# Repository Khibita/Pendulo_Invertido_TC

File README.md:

# 🧩 Proyecto: Péndulo Invertido

## 📋 Introducción
Este proyecto se centra en diseñar, construir y poner en marcha un péndulo invertido. Este es un sistema muy conocido en ingeniería de control porque es un ejemplo clásico de un sistema que no es lineal, es inestable y además tiene doble integración. 

El péndulo invertido presenta un desafío interesante, ya que hay que crear un sistema de control capaz de mantenerlo en equilibrio vertical desde cualquier posición inicial y frente a perturbaciones externas. Para lograrlo, se ha implementado un controlador PID usando un microcontrolador ESP32, apoyado por sensores de orientación como acelerómetro y giroscopio, y un sistema de actuadores con motores DC. 

Durante el desarrollo del proyecto, se han trabajado distintas áreas como:
- [ ] el diseño y fabricación del sistema mecánico con impresión 3D.
- [ ] la selección e integración de componentes electrónicos.
- [ ] la programación del controlador en el entorno Arduino y la sintonización del PID para validar el comportamiento del sistema.

Al final, se ha logrado crear un robot que puede mantenerse en posición vertical, resistir pequeñas perturbaciones y desplazarse controladamente. Todo el proceso está bien documentado y puedes consultarlo y reutilizarlo en este repositorio.

---

## 🎯 Objetivos
- [ ] Estabilidad en posición vertical (±5°)
- [ ] Compensación de empujones
- [ ] Arranque desde cualquier posición
- [ ] Implementación en ESP32
- [ ] Sintonización del PID

---

## 🛠️ Hardware
**Componentes usados:**
- [ ] ESP32: [WROOM 32D], elegimos está por su bajo costé, conexiones inalambricas y poder ejecutar codigo c.
- [ ] Sensor: [MPU9250], elegimos está por su bajo costé, y devolver aceleración en 9 ejes.
- [ ] Driver de motor: [TB6612FNG] se ajustaba a las caracteristicas necesarias
- [ ] Motores: [fz3176] Motor de corriente continua que se ajustaba al precio y potencia de consumo
- [ ] Batería: [ MN1604] Coloquialemente conocida de "petaca", produce 9V de alimentación, El sistema necesita más , conexión por cable, para siguie
- [ ] Regulador de Tensión: [LM7805]
- [ ] Condensador: [0.1uF y 0.2uf]
- [ ] Conectores entrada y salida :  3 de 2 pines.

-Recordar que tanto la conexión electrica , como la pcb se adjunta en este mismo repositorio.

---

## 🧱 Diseño mecánico
**Software de diseño usado:**  
- [ ] Para está pieza de geometría simple, pero que contaba con multiples caras, elegí freecad, debido que es con el estoy familiarizado por otras asignaturas y por tener entornos bien organizados y una comunidad activa. Aunque si es tu primera vez realizando este tipo de objetos con varias caras, te recomiendo aplicaciones con interfaces más modernas.

**Método de fabricación:**  
- [ ] Impresora 3D, en concreto la Anet A8. La impresión tardará bastante por culpa de los soportes, para reducir el tiempo, se podría probar o a inclinar la figura o rotar la figura para que el eje y quede como el eje x, precauición  son sujerencias no validadas. 

**Versiones del chasis y decisiones de diseño:**  
- [ ] Solo hay una versión, la publicada, en la cual prioricé que el centro de masas fuera lo más bajo posible y que estuviera centrado, apare de que no fuera necesario, tornillos más que para la placa base, aunque por como está  encastrada, no sería necesaría pasa su funcionamiento, recomiendo encarecidamente pornerlos.Para buscar un balance entre centro de masas bajo y porcentaje de ángulo de giro libre de las ruedas , sin que el chasis toque suelo, hice una incisio (diminuir el espesor a 1) en la parte baja del chasis un rectangulo para colocar la bateria , en caso de usar un portapilas más grande o una batería que superé las dimensiones de la usada habría que modificar el chasis.

---

## 🔌 Montaje
El montaje se divide en 2 partes:
- [ ] Soldar: soldar todos los componentes a la placa, en caso de querer reutilizar los componentes, recomiendo soldar conectores macho hembra a la placa en vez de los propios componentes. IMPORTANTE SEGUIR LAS DIRECCIONES DE LA PCB .
- [ ] Colocar las piezas: recomiendo empezar por la pcb una vez atornillada, seguir con los motores y por último pegar la batería con silicona al hueco posterior a la placa. 
---

## 📈 Control y software
**Controlador:** PID

**Implementación:**  
El lenguaje es .ino, compatible con  Esp32, pero las libreria en las que se basa, los pids a utilizar, está escrita en c++.

**Valores de cte del PID (Op 1 - reajustes pequeños en valores cercanos al (0,0), pero resistente a golpes fuertes):**  
- [ ] Kp = 50.0
- [ ] Ki = 1.0
- [ ] Kd = 20.0

**Valores de cte del PID (Op 1 - se mantiene quieto totalmente, pero sensible a golpes fuertes):**  
- [ ] Kp = 50.0
- [ ] Ki = 2.0
- [ ] Kd = 20.0

**PID Seleccionado**
- [ ] PID Filtrado, opción 3.

De forma resumida el codigo  compara el setpoint (posición destino) y la actual, a través del pid seleccionado, devuelve valores para los motores, que luego de ser normalizador , para enviar a los motores.

---

🎮 Control Inalambrico:

implementé la conexión por Bluetooth para que el sistema pudiera recibir órdenes en tiempo real desde un celular o una app, en mi caso serial terminal bluetooth, como si fuera un control remoto. Lo que hago es leer dos valores que llegan separados por una coma: uno controla el movimiento hacia adelante o atrás, y el otro el giro. Con esos datos, ajusto el setpoint del controlador PID para que el sistema se mueva según lo que el usuario indique, y también modifico la señal de los motores para que pueda girar fácilmente. Además, hice que el sistema mande de vuelta los valores recibidos por Bluetooth, así se puede ver desde el celular que la señal llegó bien y todo está funcionando como se espera.

---

## Resultados
**Hay que distingir dos casos según los valores de Kp, Ki, Kd elegidos:**
- [ ] Op 1:  El sistema llega conseguir estabilizarse en la mayoría de casos a golpes que incluso hagan tocar el suelo con el chasis. Una vez estabilizado empieza a tener pequeños sobre ajustes que hace que oscile un poco.
- [ ] Op 2:  El sistema consigue estabilizarse con golpes pequeños, pero en el caso de que el chasis toque suelo, no será capaz de conseguir levantarse de nuevo hasta chocar con algún objeto. Una vez estabilizado se mantiene estatico.

En resumen dependiendo de la respuestá deseada se puede elegir una u otra e incluso otras convinaciones de Kp, Ki y Kd. 

**Problemas con la Potencia**
- [ ] la conexión bluetooth hace que pierde algo de potencia los motores, por lo que es más sensible a perturbaciones, esto es debido a que el sistema no está pensado para una batería tan sencilla.
- [ ] Problemas de potencia, al romperseme los dos portapilas con que contaba tuve que hacer un arreglo con una batería de 9v auxiliar, por lo que se necesita conectar el robot a una fuente de energía. 

---

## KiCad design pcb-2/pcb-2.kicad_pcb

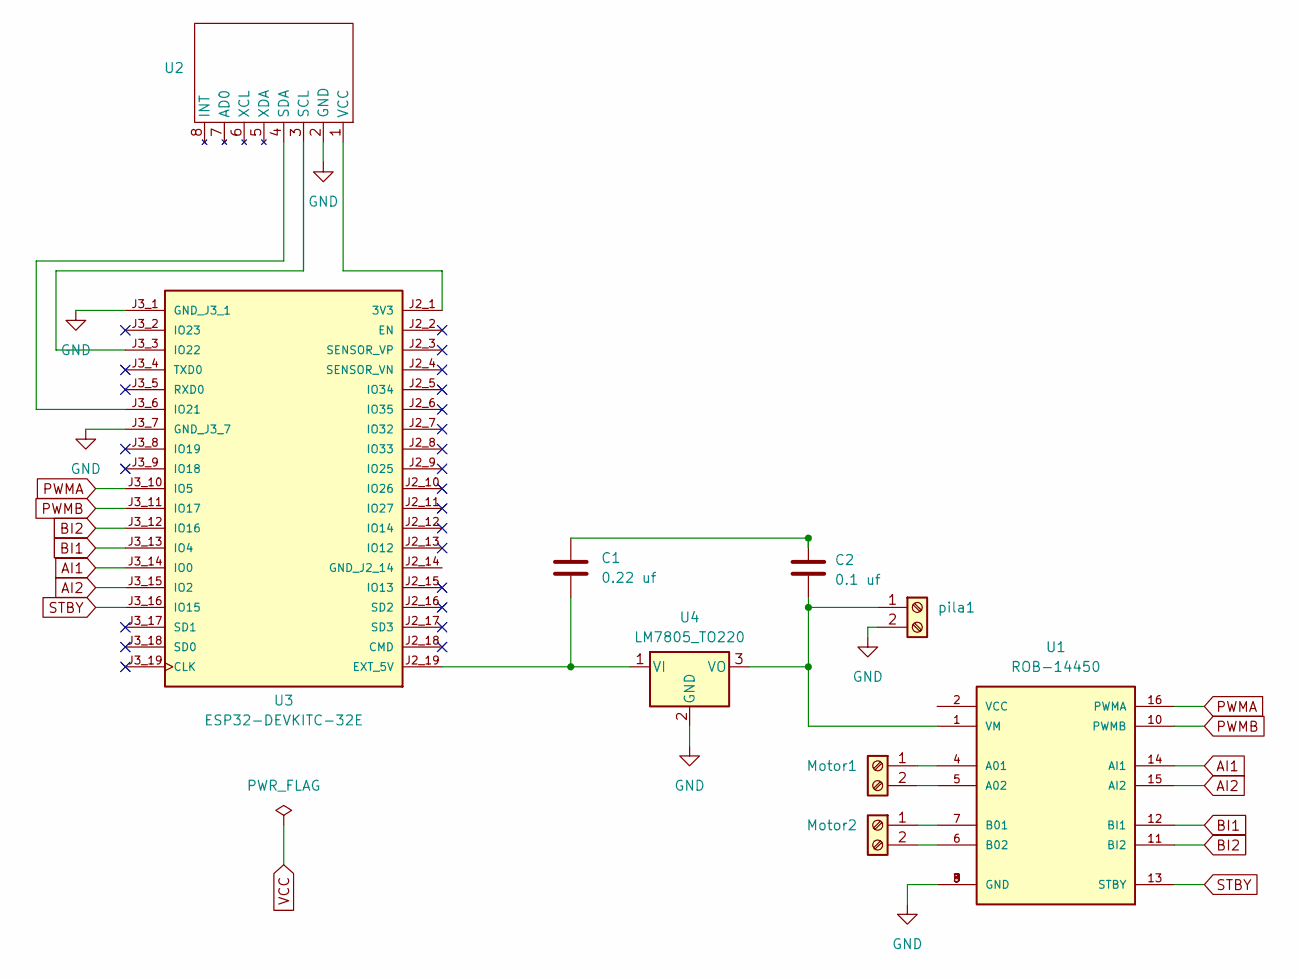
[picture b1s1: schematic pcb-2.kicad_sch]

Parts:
C1: 0.22 uf; CP_Radial_D5.0mm_P2.00mm
C2: 0.1 uf; CP_Radial_D5.0mm_P2.00mm
Motor1, Motor2: TerminalBlock_Phoenix_MKDS-1,5-2-5.08_1x02_P5.08mm_Horizont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
U1: ROB-14450; MODULE_ROB-14450; PARTREV 11-13-17
U2: MPU-6050
U3: ESP32-DEVKITC-32E; MODULE_ESP32-DEVKITC-32E; PARTREV 1.4
U4: LM7805_TO220; TO-220-3_Vertical
pila1: TerminalBlock_Phoenix_MKDS-1,5-2-5.08_1x02_P5.08mm_Horizont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

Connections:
AI1: U1.14 (AI1), U3.J3_14 (IO0)
AI2: U1.15 (AI2), U3.J3_15 (IO2)
BI1: U1.12 (BI1), U3.J3_13 (IO4)
BI2: U1.11 (BI2), U3.J3_12 (IO16)
GND: U1.3 (GND), U1.8 (GND), U1.9 (GND), U2.2 (GND), U3.J3_1 (GND_J3_1), U3.J3_7 (GND_J3_7), U4.2 (GND), pila1.2
unnamed: C1.1, C2.1
unnamed: Motor1.1, U1.4 (A01)
unnamed: Motor1.2, U1.5 (A02)
unnamed: Motor2.1, U1.7 (B01)
unnamed: Motor2.2, U1.6 (B02)
unnamed: C2.2, U1.1 (VM), U4.3 (VO), pila1.1
unnamed: U2.3 (SCL), U3.J3_3 (IO22)
unnamed: U2.4 (SDA), U3.J3_6 (IO21)
unnamed: U2.1 (VCC), U3.J2_1 (3V3)
unnamed: C1.2, U3.J2_19 (EXT_5V), U4.1 (VI)
PWMA: U1.16 (PWMA), U3.J3_10 (IO5)
PWMB: U1.10 (PWMB), U3.J3_11 (IO17)
STBY: U1.13 (STBY), U3.J3_16 (IO15)

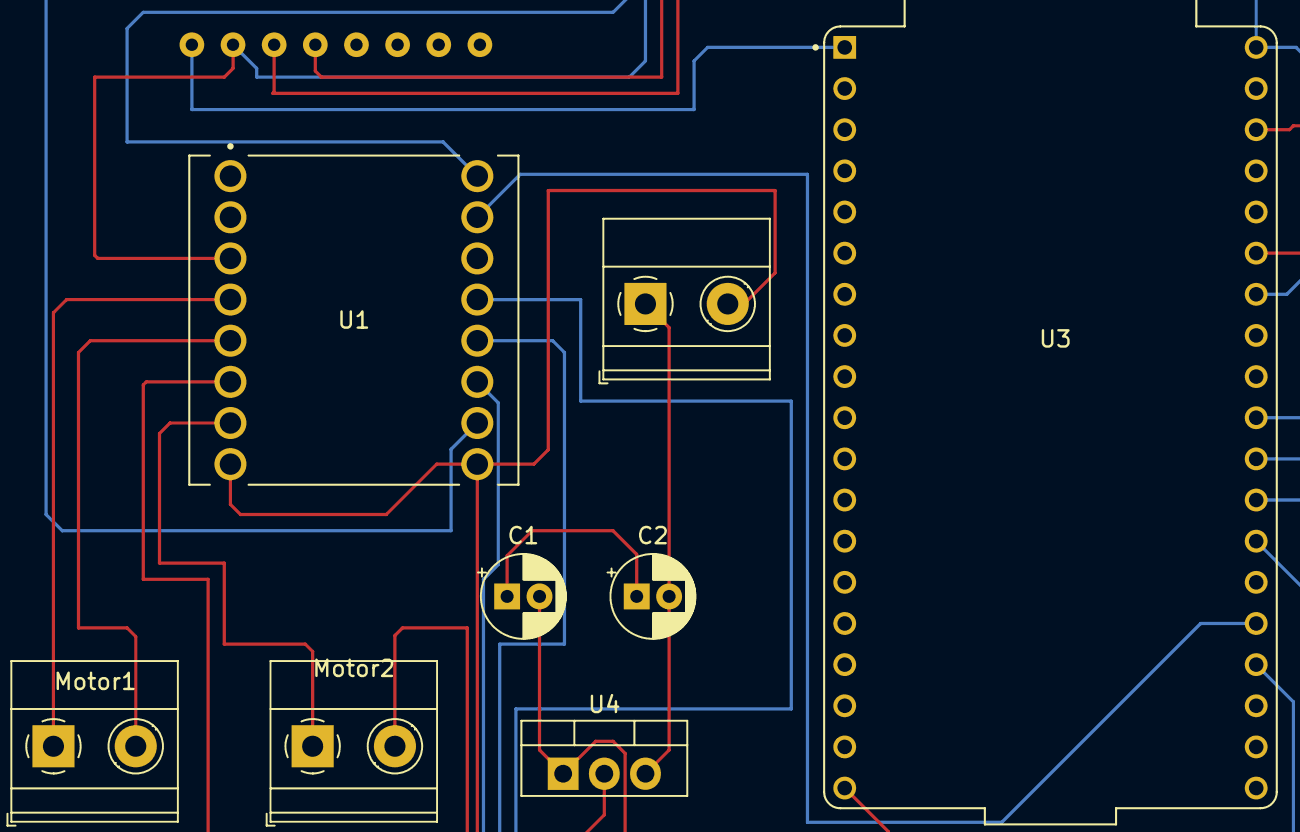
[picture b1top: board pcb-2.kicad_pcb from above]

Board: 2 copper layers, 9 parts (0 on the bottom side), 18 nets.

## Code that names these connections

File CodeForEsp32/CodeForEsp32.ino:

#include <Wire.h>
#include <MPU6050.h>
#include "PIDControl.h"
#include <BluetoothSerial.h>

int PID_MODE = 3; //Variable de control 
float dt = 0.005; //Periodo de actualizacion del void loop, EN SEGUNDOS
unsigned long dt_us = dt * 1e6; //Lo pasamos a microsegundos

MPU6050 mpu;
BluetoothSerial SerialBT;

const int AIN1 = 0, AIN2 = 2, PWMA = 5;
const int BIN1 = 4, BIN2 = 16, PWMB = 17;
const int STBY = 15;

//Valores, para el estado 0
float setpoint = 0.0;
float measured_value = 0.0;
float output = 0;

float desplazamientoX = 0.0;
float desplazamientoY = 0.0;

//Constantes del pid a implementar
float kp =50.0, ki = 1, kd = 20.0;

//Definimos un objeto pid, por ahora no asigmanos ninguo
PID* pid = nullptr;

void setup() {
  Serial.begin(115200);
  SerialBT.begin("ESP32Khibita");  // Nombre del dispositivo Bluetooth
  Wire.begin();
  mpu.initialize();

  //AINX y BINX pines de direccion de vel, mientras PWMX modulo de velocidad
  pinMode(AIN1, OUTPUT); pinMode(AIN2, OUTPUT); pinMode(PWMA, OUTPUT);
  pinMode(BIN1, OUTPUT); pinMode(BIN2, OUTPUT); pinMode(PWMB, OUTPUT);
  pinMode(STBY, OUTPUT); digitalWrite(STBY, HIGH);

  switch (PID_MODE) { //Elegir cual de las 3 implementacion usar
    case 1:
      pid = new PID_Discreto(kp, ki, kd, dt);
      break;
    case 2:
      pid = new PID_IIR(kp, ki, kd, dt);
      break;
    case 3:
    default:
      pid = new PID_Filtrado(kp, ki, kd, dt, 5.0);
      break;
  }
}

float getAngle() { //angulo para el plano YZ, EN GRADOS
  int16_t ax, ay, az;
  mpu.getAcceleration(&ax, &ay, &az);
  return atan2(ay, az) * 180 / PI;
}

void applyMotorA(float pwm) {
  pwm = constrain(pwm, -255, 255);
  digitalWrite(AIN1, pwm > 0 ? HIGH : LOW);
  digitalWrite(AIN2, pwm > 0 ? LOW : HIGH);
  analogWrite(PWMA, abs(pwm));
}

void applyMotorB(float pwm) {
  pwm = constrain(pwm, -255, 255);
  digitalWrite(BIN1, pwm > 0 ? HIGH : LOW);
  digitalWrite(BIN2, pwm > 0 ? LOW : HIGH);
  analogWrite(PWMB, abs(pwm));
}



void loop() {
  static unsigned long lastControl = 0;
  unsigned long now = micros(); //Devuelve los msec 
  if (now - lastControl >= dt_us) { 
    lastControl = now;

    measured_value = getAngle();
    output = pid->compute(setpoint, measured_value);
    output = constrain(output, -255, 255); // normalizar a los rangos de los motroes

    if (SerialBT.available()) { //En caso de tener Comunicacion bluethoot
      String datos = SerialBT.readStringUntil('\n');
      int sep = datos.indexOf(',');
      if (sep > 0) {
        float x = datos.substring(0, sep).toFloat();
        float y = datos.substring(sep + 1).toFloat();
        desplazamientoX = x;
        desplazamientoY = y;
        setpoint += desplazamientoY * 0.03;
      }
    }

    float pwmGiro = desplazamientoX * 2.55;
    
    //Valors para los dos motores , se resta o se suma dependiendo del sentido de giro
    applyMotorA(output - pwmGiro);
    applyMotorB(output + pwmGiro);
     
     
     
        // Enviar valores de vuelta por Bluetooth
    SerialBT.print("Recibido -> X: ");
    SerialBT.print(desplazamientoX, 2); // dos decimales
    SerialBT.print(" Y: ");
    SerialBT.println(desplazamientoY, 2);
  }
}
